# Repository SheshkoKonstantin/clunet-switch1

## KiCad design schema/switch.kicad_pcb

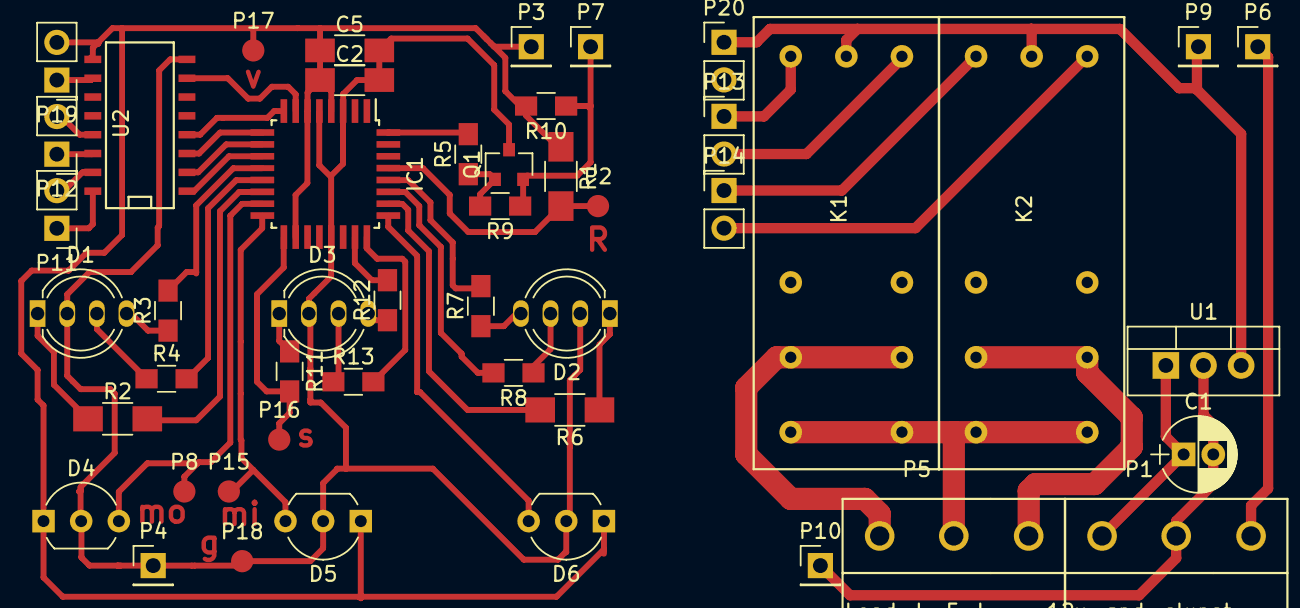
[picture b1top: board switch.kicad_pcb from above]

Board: 2 copper layers, 48 parts (0 on the bottom side), 48 nets.

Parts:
C1: 100mkf; CP_Radial_D5.0mm_P2.00mm
C2: 10mkf; C_1206_HandSoldering
C5: C_Small; C_1206_HandSoldering
D1, D2, D3: Led1; LED_D5.0mm-4-LL
D4, D5, D6: AH201; TO-92_Inline_Wide
IC1: ATMEGA8A-A; TQFP-32_7x7mm_Pitch0.8mm-LUT
K1, K2: RT424F05
P1: 12v-gnd-clunet; DG301-5.0-3x
P2: Reset; Measurement_Point_Round-SMD-Pad_Small
P3, P9: Vcc; Socket_Strip_Straight_1x01_Pitch2.54mm
P4, P10: Gnd; Socket_Strip_Straight_1x01_Pitch2.54mm
P5: Load-L-F-L; DG301-5.0-3x
P6, P7: Clunet; Socket_Strip_Straight_1x01_Pitch2.54mm
P8: CON_MOS; Measurement_Point_Round-SMD-Pad_Small
P11, P13: R1_; Socket_Strip_Straight_1x02_Pitch2.54mm
P12, P14: R2_; Socket_Strip_Straight_1x02_Pitch2.54mm
P15: CON_MIS; Measurement_Point_Round-SMD-Pad_Small
P16: CON_SCK; Measurement_Point_Round-SMD-Pad_Small
P17: Vcc_Prog; Measurement_Point_Round-SMD-Pad_Small
P18: Gnd_Prog; Measurement_Point_Round-SMD-Pad_Small
P19, P20: SPK; Socket_Strip_Straight_1x02_Pitch2.54mm
Q1: PNP BC858; SOT-23
R1: 1.5K; R_1206_HandSoldering
R2, R6: 470R; R_1206_HandSoldering
R3, R4, R7, R8, R11, R12, R13: 470R; R_0805_HandSoldering
R5: 2.2K; R_0805_HandSoldering
R9: 22K; R_0805_HandSoldering
R10: 560R; R_0805_HandSoldering
U1: 7805; TO-220_Vertical-LM7805
U2: ULN2003-norm; SO-16-N

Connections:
+5V: K1.3, K2.3, P9.1, P20.1, U1.VO
+12V: C1.1, P1.1, U1.VI
/LED1_1: IC1.14, R2.2
/LED1_2: IC1.13, R4.2
/LED1_3: IC1.12, R3.2
/LED2_1: IC1.17, P16.1, R11.2
/LED2_2: IC1.23, R12.2
/LED2_3: IC1.24, R13.2
/LED3_1: IC1.26, R6.2
/LED3_2: IC1.27, R8.2
/LED3_3: IC1.28, R7.2
/R1_1: IC1.11, U2.1
/R1_2: IC1.10, U2.2
/R2_1: IC1.9, U2.3
/R2_2: IC1.8, U2.4
/SW1: D4.3, IC1.15, P8.1
/SW2: D5.3, IC1.16, P15.1
/SW3: D6.3, IC1.25
/spk: IC1.7, U2.7
GND: C2.2, C5.2, D1.2, D2.2, D3.2, D4.2, D5.2, D6.2, IC1.3, IC1.5, IC1.21, P4.1, P18.1, Q1.3, U2.8
GNDA: C1.2, P1.2, P10.1, U1.GND
unnamed: D1.1, R2.1
unnamed: D1.3, R4.1
unnamed: D1.4, R3.1
unnamed: D2.1, R6.1
unnamed: D2.3, R8.1
unnamed: D2.4, R7.1
unnamed: D3.1, R11.1
unnamed: D3.3, R13.1
unnamed: D3.4, R12.1
unnamed: IC1.29, P2.1, R1.2
unnamed: IC1.32, R5.2
unnamed: K1.1, P13.2
unnamed: K1.2, P13.1
unnamed: K1.11, K1.21, P5.1
unnamed: K1.14, K1.24, K2.14, K2.24, P5.2
unnamed: K2.1, P14.2
unnamed: K2.2, P14.1
unnamed: K2.11, K2.21, P5.3
unnamed: P1.3, P6.1
unnamed: P11.1, U2.16
unnamed: P11.2, U2.15
unnamed: P12.1, U2.14
unnamed: P12.2, U2.13
unnamed: P19.1, U2.10
unnamed: Q1.1, R5.1, R9.2
VCC: C2.1, C5.1, D4.1, D5.1, D6.1, IC1.4, IC1.6, IC1.18, P3.1, P17.1, P19.2, R1.1, R10.2, U2.9
clunet: P7.1, Q1.2, R9.1, R10.1

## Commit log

2017-03-20 Первый комит Здесь уже было много изменений. Пора бы начать репозиторй
2017-03-20 Добавлен КлуНет
2017-03-20 Недостающие файлы схемы
2017-03-21 Изменил тактовые кнопки на датчики Холла
2017-03-24 Добавление крышки
2017-04-09 Какие-то еще небольшие изменения в корпусе Напечатался не плохо
2017-04-09 add makefile
2017-04-09 Попытка привести все в порядок
2017-04-09 Фото
2017-04-09 Добавлены схема и разводка в PDF
